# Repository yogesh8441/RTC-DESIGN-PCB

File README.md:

# RTC Design PCB

## 📌 Overview

This project is a Real-Time Clock (RTC) PCB designed using KiCad. It provides accurate date and time keeping for embedded systems.

## ✨ Features

- Real-Time Clock Circuit
- 2-Layer PCB Design
- Compact PCB Layout
- ERC and DRC Checked
- Manufacturing Ready Gerber Files

## 🛠 Software Used

- KiCad 10.0

## 📂 Project Files

- KiCad Project (.kicad_pro)
- Schematic (.kicad_sch)
- PCB Layout (.kicad_pcb)
- Gerber Files
- Project Images

## 📷 Project Images

### Schematic

### PCB Layout

### Top 3D View

### Bottom 3D View

## 📦 Gerber Files

All manufacturing Gerber files are available in the **Gerber** folder.

## 👨‍💻 Author

**Yogesh Kumar**

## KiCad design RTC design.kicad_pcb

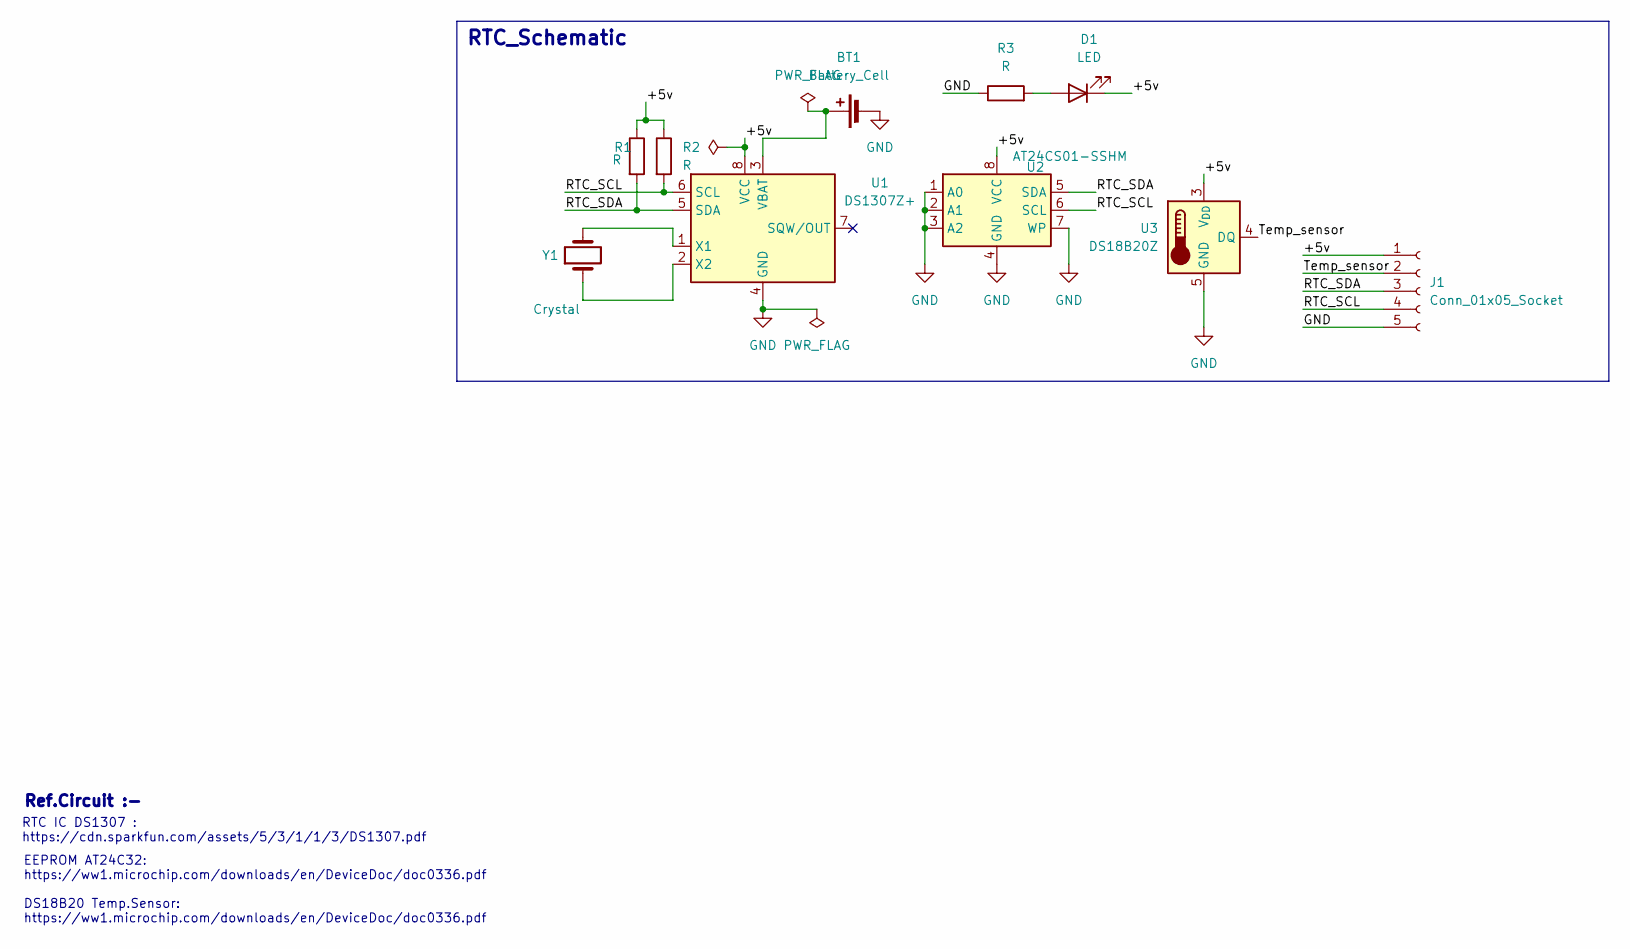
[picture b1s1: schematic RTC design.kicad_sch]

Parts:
BT1: Battery_Cell; BatteryHolder_Keystone_1060_1x2032
D1: LED; LED_0201_0603Metric
J1: Conn_01x05_Socket; PinHeader_1x05_P2.54mm_Vertical_SMD_Pin1Right
R1, R2, R3: R; R_0402_1005Metric
U1: DS1307Z+; SOIC-8_3.9x4.9mm_P1.27mm
U2: AT24CS01-SSHM; SOIC-8_3.9x4.9mm_P1.27mm
U3: DS18B20Z; SOIC-8_3.9x4.9mm_P1.27mm
Y1: Crystal; Crystal_HC52-8mm_Vertical

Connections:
/+5v: D1.1 (K), J1.1, R1.1, R2.1, U1.8 (VCC), U2.8 (VCC), U3.3 (V_{DD})
/RTC_SCL: J1.4, R2.2, U1.6 (SCL), U2.6 (SCL)
/RTC_SDA: J1.3, R1.2, U1.5 (SDA), U2.5 (SDA)
/Temp_sensor: J1.2, U3.4 (DQ)
GND: BT1.2 (-), J1.5, R3.1, U1.4 (GND), U2.1 (A0), U2.2 (A1), U2.3 (A2), U2.4 (GND), U2.7 (WP), U3.5 (GND)
unnamed: BT1.1 (+), U1.3 (VBAT)
unnamed: D1.2 (A), R3.2
unnamed: U1.1 (X1), Y1.2
unnamed: U1.2 (X2), Y1.1

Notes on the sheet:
RTC_Schematic
RTC IC DS1307 : https://cdn.sparkfun.com/assets/5/3/1/1/3/DS1307.pdf
EEPROM AT24C32: https://ww1.microchip.com/downloads/en/DeviceDoc/doc0336.pdf
DS18B20 Temp.Sensor: https://ww1.microchip.com/downloads/en/DeviceDoc/doc0336.pdf
Ref.Circuit :-

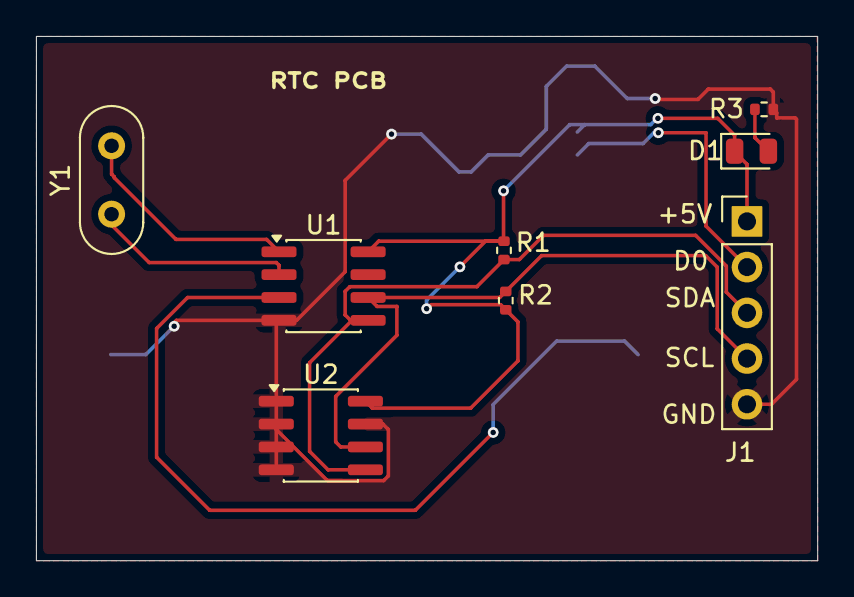
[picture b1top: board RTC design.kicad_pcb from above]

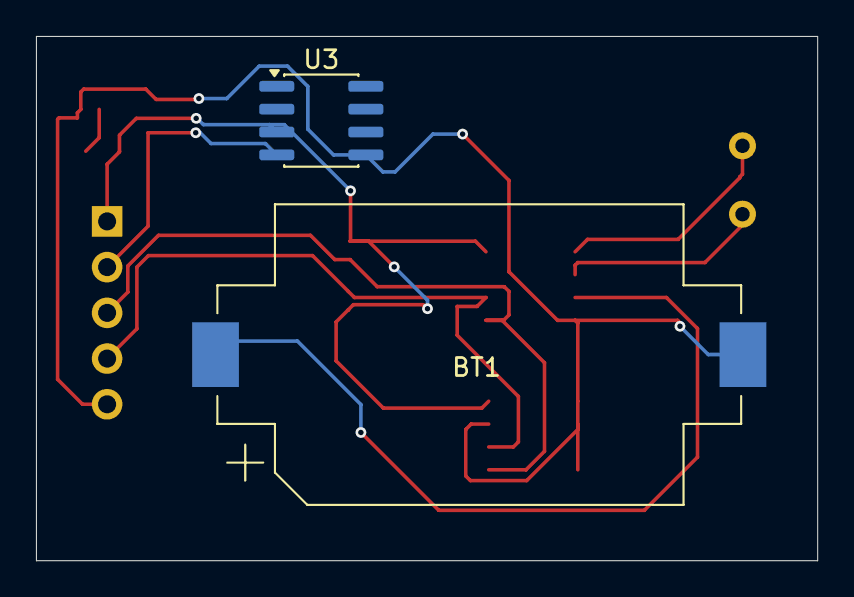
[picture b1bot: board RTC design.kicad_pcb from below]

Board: 2 copper layers, 43.4 x 29.1 mm, 10 parts (2 on the bottom side), 9 nets.
